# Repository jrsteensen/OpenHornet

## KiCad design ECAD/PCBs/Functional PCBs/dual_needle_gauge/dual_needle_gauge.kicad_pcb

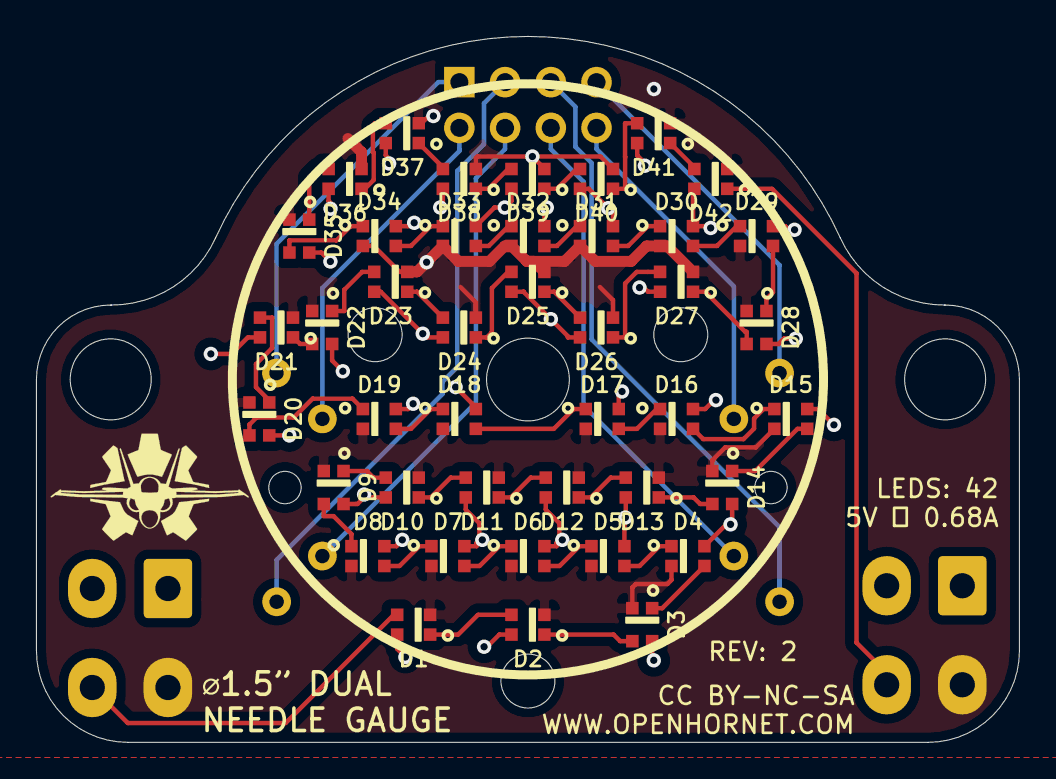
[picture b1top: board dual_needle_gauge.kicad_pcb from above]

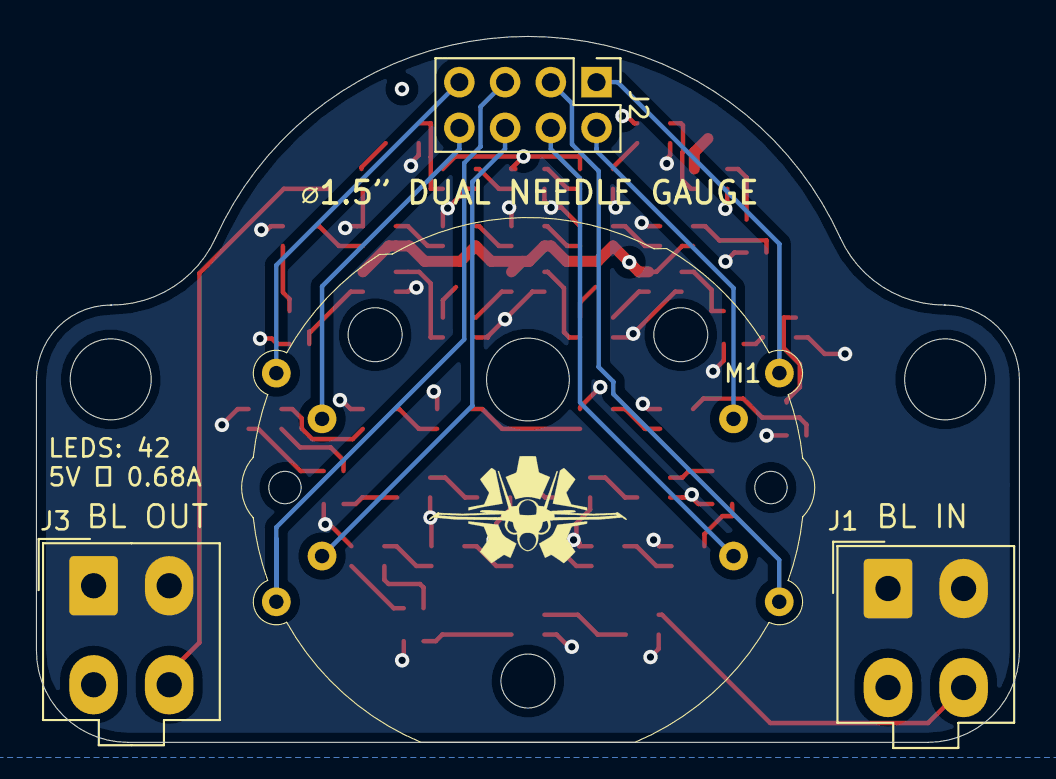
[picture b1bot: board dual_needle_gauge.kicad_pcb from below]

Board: 4 copper layers, 54.6 x 39.2 mm, 48 parts (3 on the bottom side), 53 nets.

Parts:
D1, D2, D3, D4, D5, D6, D7, D8, D9, D10, D11, D12, D13, D14, D15, D16, D17, D18, D19, D20, D21, D22, D23, D24, D25, D26, D27, D28, D29, D30, D31, D32, D33, D34, D35, D36, D37, D38, D39, D40, D41, D42: WS2812B-2020; WS2812-2020
H1, H2: MountingHole; MountingHole_4.5mm
J1: BL IN; Molex_Mini-Fit_Jr_5566-04A_2x02_P4.20mm_Vertical
J2: DATA; PinHeader_2x04_P2.54mm_Vertical
J3: BL OUT; Molex_Mini-Fit_Jr_5566-04A_2x02_P4.20mm_Vertical
M1: X40_8798; x40_8798

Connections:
/COIL1: J2.1, M1.1
/COIL2: J2.3, M1.2
/COIL3: J2.7, M1.3
/COIL4: J2.5, M1.4
/COIL5: J2.2, M1.5
/COIL6: J2.4, M1.6
/COIL7: J2.8, M1.7
/COIL8: J2.6, M1.8
/DIN: D1.3, J1.4
/DOUT: D42.1, J3.4
/DOUT1: D10.1, D11.3
/DOUT2: D20.1, D21.3
/DOUT3: D30.1, D31.3
/DOUT4: D40.1, D41.3
/LED+5V: D1.4, D2.4, D3.4, D4.4, D5.4, D6.4, D7.4, D8.4, D9.4, D10.4, D11.4, D12.4, D13.4, D14.4, D15.4, D16.4, D17.4, D18.4, D19.4, D20.4, D21.4, D22.4, D23.4, D24.4, D25.4, D26.4, D27.4, D28.4, D29.4, D30.4, D31.4, D32.4, D33.4, D34.4, D35.4, D36.4, D37.4, D38.4, D39.4, D40.4, D41.4, D42.4, J1.1, J1.2, J3.1, J3.2
/LEDGND: D1.2, D2.2, D3.2, D4.2, D5.2, D6.2, D7.2, D8.2, D9.2, D10.2, D11.2, D12.2, D13.2, D14.2, D15.2, D16.2, D17.2, D18.2, D19.2, D20.2, D21.2, D22.2, D23.2, D24.2, D25.2, D26.2, D27.2, D28.2, D29.2, D30.2, D31.2, D32.2, D33.2, D34.2, D35.2, D36.2, D37.2, D38.2, D39.2, D40.2, D41.2, D42.2, J1.3, J3.3
unnamed: D1.1, D2.3
unnamed: D2.1, D3.3
unnamed: D3.1, D4.3
unnamed: D4.1, D5.3
unnamed: D5.1, D6.3
unnamed: D6.1, D7.3
unnamed: D7.1, D8.3
unnamed: D8.1, D9.3
unnamed: D9.1, D10.3
unnamed: D11.1, D12.3
unnamed: D12.1, D13.3
unnamed: D13.1, D14.3
unnamed: D14.1, D15.3
unnamed: D15.1, D16.3
unnamed: D16.1, D17.3
unnamed: D17.1, D18.3
unnamed: D18.1, D19.3
unnamed: D19.1, D20.3
unnamed: D21.1, D22.3
unnamed: D22.1, D23.3
unnamed: D23.1, D24.3
unnamed: D24.1, D25.3
unnamed: D25.1, D26.3
unnamed: D26.1, D27.3
unnamed: D27.1, D28.3
unnamed: D28.1, D29.3
unnamed: D29.1, D30.3
unnamed: D31.1, D32.3
unnamed: D32.1, D33.3
unnamed: D33.1, D34.3
unnamed: D34.1, D35.3
unnamed: D35.1, D36.3
unnamed: D36.1, D37.3
unnamed: D37.1, D38.3
unnamed: D38.1, D39.3
unnamed: D39.1, D40.3
unnamed: D41.1, D42.3

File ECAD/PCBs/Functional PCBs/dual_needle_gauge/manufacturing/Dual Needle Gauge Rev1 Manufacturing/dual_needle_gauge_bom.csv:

Comment,Designator,Footprint,LCSC
"WS2812B-2020","D1,D2,D3,D4,D5,D6,D7,D8,D9,D10,D11,D12,D13,D14,D15,D16,D17,D18,D19,D20,D21,D22,D23,D24,D25,D26,D27,D28,D29,D30,D31,D32,D33,D34,D35,D36,D37,D38,D39,D40,D41,D42","KiCAD Libraries:WS2812-2020","C965555"
"MountingHole","H1,H2","MountingHole:MountingHole_4.5mm",""
"BL IN","J1","Connector_Molex:Molex_Mini-Fit_Jr_5566-04A_2x02_P4.20mm_Vertical",""
"DATA","J2","Connector_PinHeader_2.54mm:PinHeader_2x04_P2.54mm_Vertical",""
"BL OUT","J3","Connector_Molex:Molex_Mini-Fit_Jr_5566-04A_2x02_P4.20mm_Vertical",""
"X40_8798","M1","KiCAD Libraries:x40_8798",""

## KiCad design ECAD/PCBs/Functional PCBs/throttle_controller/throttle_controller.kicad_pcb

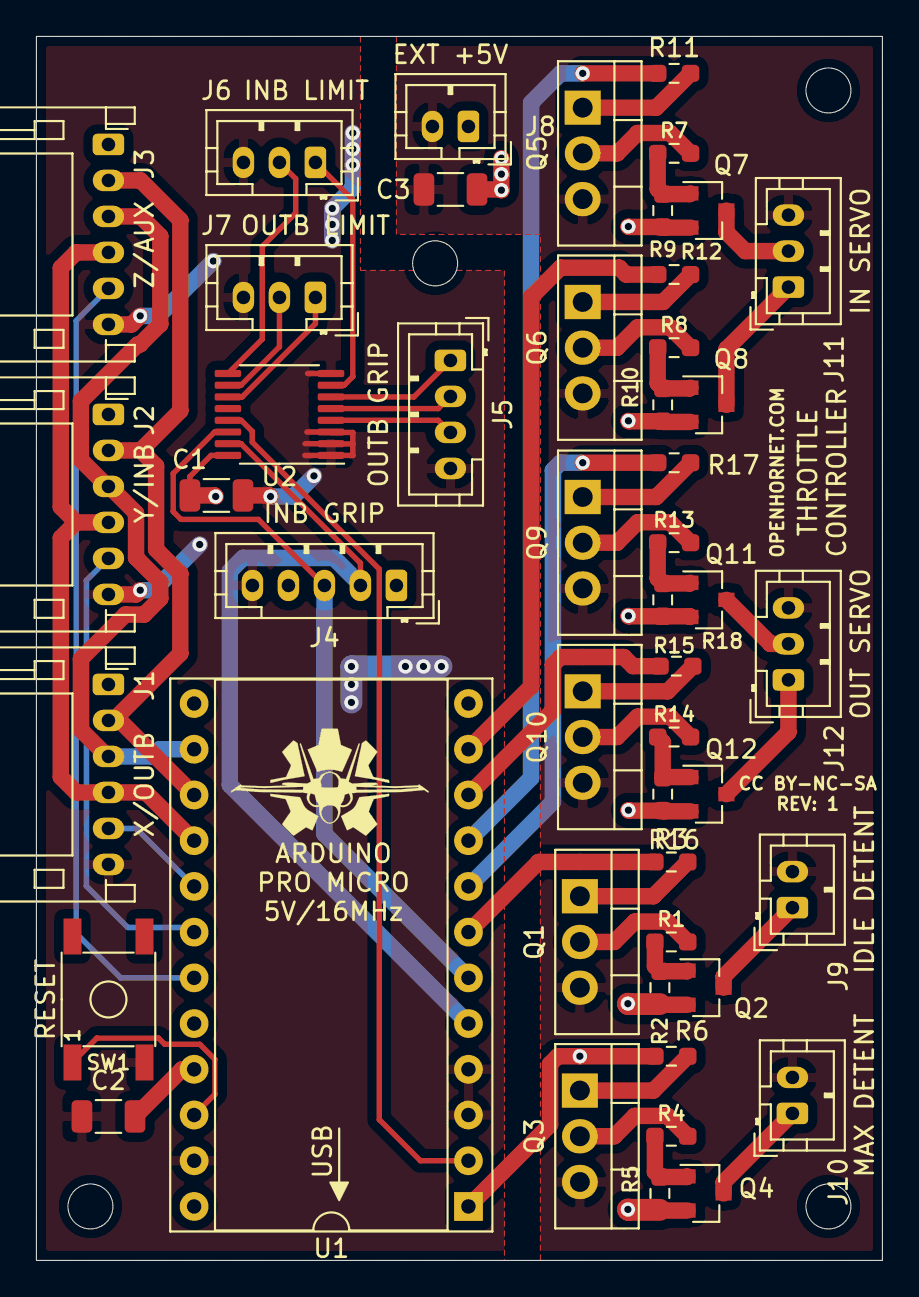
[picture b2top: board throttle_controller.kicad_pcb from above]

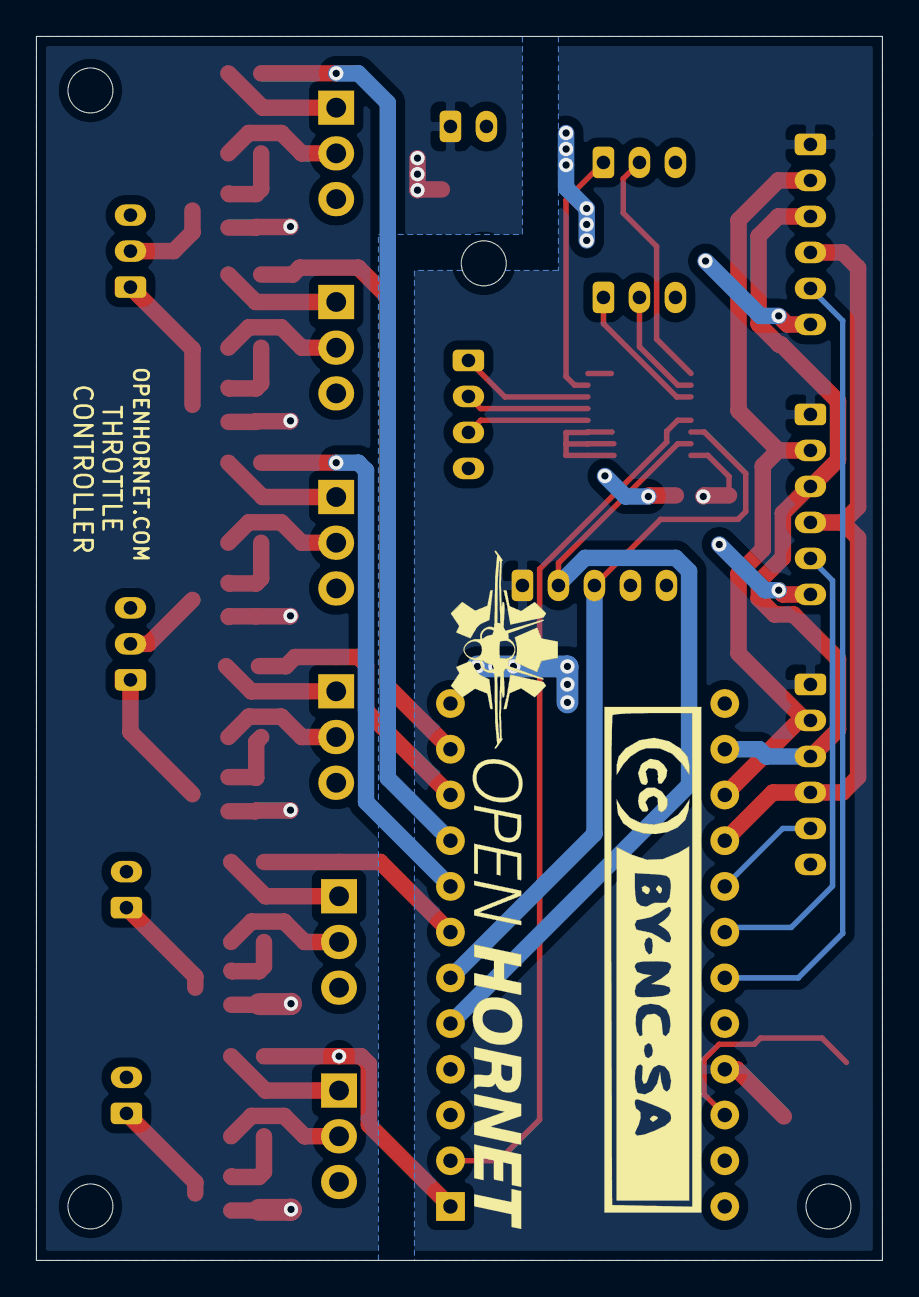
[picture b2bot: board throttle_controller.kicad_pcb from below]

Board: 2 copper layers, 47.0 x 68.0 mm, 55 parts (2 on the bottom side), 51 nets.

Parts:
C1: 47uF; C_1206_3216Metric
C2, C3: 10uF; C_1206_3216Metric
H1, H2, H3, H4: MH; MountingHole_2.5mm
J1: X/OUTB; JST_PH_S6B-PH-K_1x06_P2.00mm_Horizontal
J2: Y/INB; JST_PH_S6B-PH-K_1x06_P2.00mm_Horizontal
J3: Z/AUX; JST_PH_S6B-PH-K_1x06_P2.00mm_Horizontal
J4: INB GRIP; JST_PH_B5B-PH-K_1x05_P2.00mm_Vertical
J5: OUTB GRIP; JST_PH_B4B-PH-K_1x04_P2.00mm_Vertical
J6: INB LIMIT; JST_PH_B3B-PH-K_1x03_P2.00mm_Vertical
J7: OUTB LIMIT; JST_PH_B3B-PH-K_1x03_P2.00mm_Vertical
J8: EXT +5V; JST_PH_B2B-PH-K_1x02_P2.00mm_Vertical
J9: IDLE DETENT; JST_PH_B2B-PH-K_1x02_P2.00mm_Vertical
J10: MAX DETENT; JST_PH_B2B-PH-K_1x02_P2.00mm_Vertical
J11: IN SERVO; JST_PH_B3B-PH-K_1x03_P2.00mm_Vertical
J12: OUT SERVO; JST_PH_B3B-PH-K_1x03_P2.00mm_Vertical
LOGO1: OpenHornetLogoSmall; OH_LOGO_37.7mm_5.9mm
LOGO2: OpenHornetLogoSmall; CC-BY-NC-SA-Small
LOGO3: OpenHornetLogoSmall; OH_LOGO_ONLY_11x6mm
Q1, Q3, Q5, Q6, Q9, Q10: IRFB3206PBF; TO-220-3_Vertical
Q2, Q4, Q7, Q8, Q11, Q12: IRLML6402TRPBF; SOT-23
R1, R2, R3, R4, R5, R6, R7, R8, R9, R10, R11, R12, R13, R14, R15, R16, R17, R18: 10K; R_0603_1608Metric_Pad0.98x0.95mm_HandSolder
SW1: RESET; SMD-SW-4_5.1x5.1
U1: ProMicro; DIP-24_W15.24mm_Socket
U2: TCA9554PWR; TSSOP-16_4.4x5mm_P0.65mm

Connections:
+5V: C1.1, C2.1, J1.1, J2.1, J3.1, J4.1, U1.21, U2.16
+5VA: C3.1, J8.1, Q2.2, Q4.2, Q7.2, Q8.2, Q11.2, Q12.2, R2.2, R5.2, R9.2, R10.2, R15.2, R16.2
/CSx: J1.5, U1.17
/CSy: J2.5, U1.18
/CSz: J3.5, U1.19
/IDLE_SOL_CTRL: R3.1, U1.7
/IDLE_SOL_OUT: J9.1, Q2.3
/INB_SERVO_+5VA: J11.1, Q8.3
/INB_SERVO_PWR_CTRL: R12.1, U1.11
/IRQ: U1.2, U2.13
/MAX_SOL_CTRL: R6.1, U1.1
/MAX_SOL_OUT: J10.1, Q4.3
/MISO: J1.2, J2.2, J3.2, U1.15
/MOSI: J1.3, J2.3, J3.3, U1.14
/OUTB_SERVO_+5VA: J12.1, Q12.3
/OUTB_SERVO_PWR_CTRL: R18.1, U1.10
/RST: SW1.1, U1.22
/SCK: J1.4, J2.4, J3.4, U1.16
/SDA: J4.2, U1.5, U2.15
/U1P0: J5.1, U2.6
/U1P1: J5.2, U2.5
/U1P2: J5.3, U2.4
/U1P3: J6.1, U2.7
/U1P4: J6.2, U2.9
/U1P5: J7.2, U2.10
/U1P6: J7.1, U2.11
/~INB_SERVO_CTRL: R11.1, U1.9
/~INB_SERVO_OUT: J11.2, Q7.3
/~OUTB_SERVO_CTRL: R17.1, U1.8
/~OUTB_SERVO_OUT: J12.2, Q11.3
/~SCL: J4.3, U1.6, U2.14
GND: C1.2, C2.2, J1.6, J2.6, J3.6, J4.5, J5.4, J6.3, J7.3, SW1.3, U1.3, U1.4, U1.23, U2.1, U2.2, U2.3, U2.8
GNDA: C3.2, J8.2, J9.2, J10.2, J11.3, J12.3, Q1.3, Q3.3, Q5.3, Q6.3, Q9.3, Q10.3
unnamed: Q1.1, R3.2
unnamed: Q1.2, R1.2
unnamed: Q2.1, R1.1, R2.1
unnamed: Q3.1, R6.2
unnamed: Q3.2, R4.2
unnamed: Q4.1, R4.1, R5.1
unnamed: Q5.1, R11.2
unnamed: Q5.2, R7.2
unnamed: Q6.1, R12.2
unnamed: Q6.2, R8.2
unnamed: Q7.1, R7.1, R9.1
unnamed: Q8.1, R8.1, R10.1
unnamed: Q9.1, R17.2
unnamed: Q9.2, R13.2
unnamed: Q10.1, R18.2
unnamed: Q10.2, R14.2
unnamed: Q11.1, R13.1, R15.1
unnamed: Q12.1, R14.1, R16.1

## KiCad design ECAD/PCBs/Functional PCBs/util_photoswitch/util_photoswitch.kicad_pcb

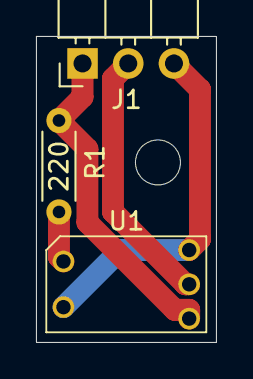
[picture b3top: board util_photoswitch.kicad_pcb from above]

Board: 2 copper layers, 10.0 x 17.0 mm, 4 parts (0 on the bottom side), 4 nets.

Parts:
H1: MountingHole; MountingHole_2.5mm
J1: Conn_01x03_Male; PinHeader_1x03_P2.54mm_Horizontal
R1: 220; R_Axial_DIN0204_L3.6mm_D1.6mm_P5.08mm_Horizontal
U1: OPB615; OPB61x

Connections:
+5V: J1.1, R1.2, U1.3
GND: J1.3, U1.2, U1.5
unnamed: J1.2, U1.4
unnamed: R1.1, U1.1

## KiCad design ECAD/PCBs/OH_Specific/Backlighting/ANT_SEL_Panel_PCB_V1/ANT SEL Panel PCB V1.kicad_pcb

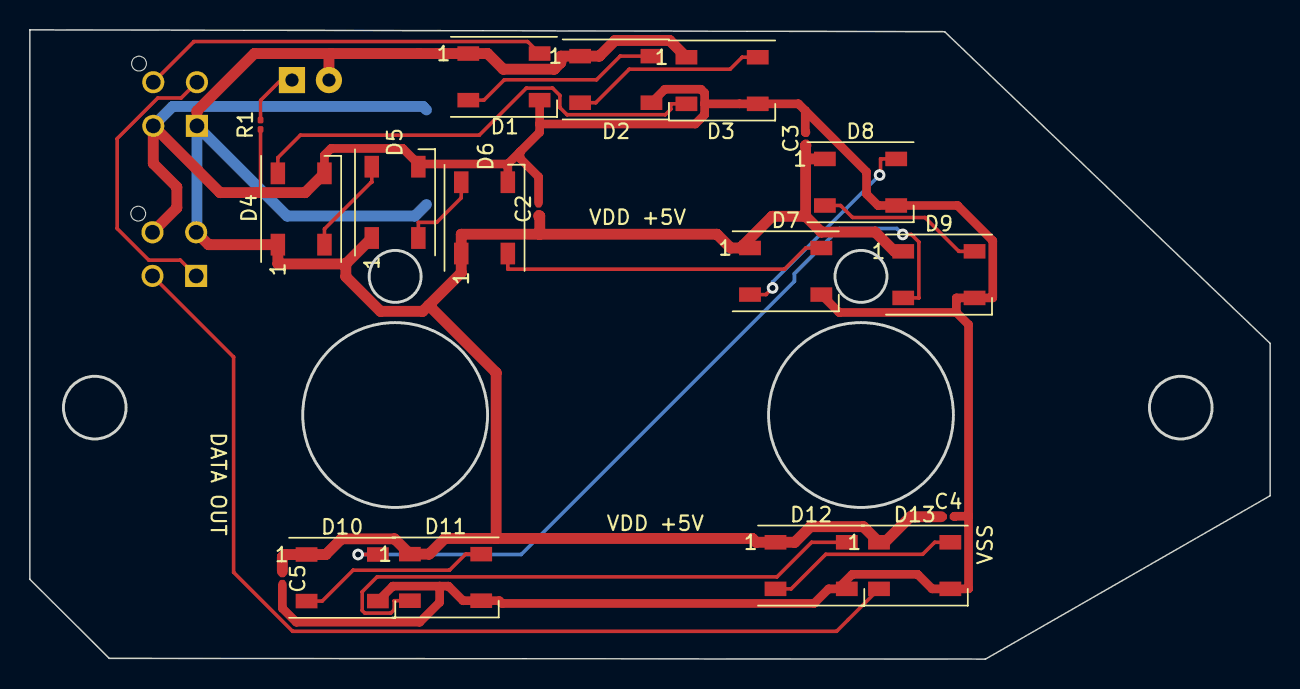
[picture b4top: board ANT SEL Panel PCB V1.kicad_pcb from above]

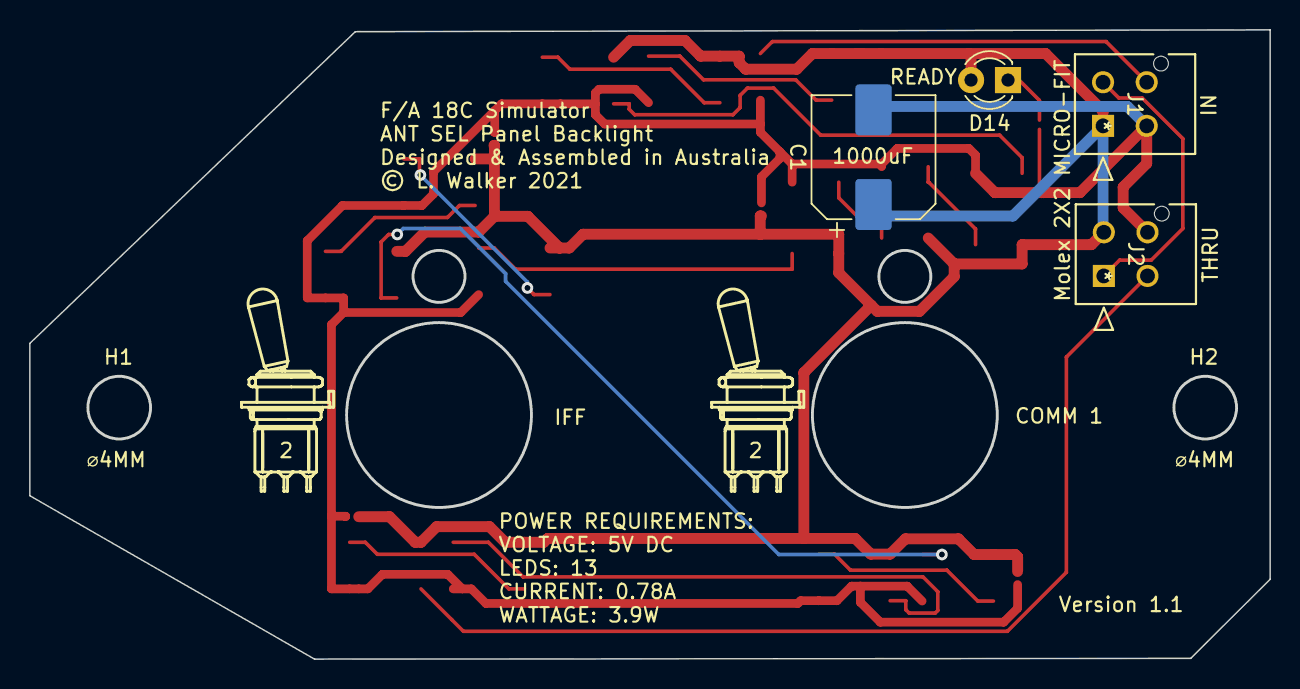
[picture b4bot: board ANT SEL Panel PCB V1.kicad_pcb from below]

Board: 2 copper layers, 85.2 x 43.2 mm, 22 parts (4 on the bottom side), 18 nets.

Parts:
C1: C_Polarized; CP_Elec_8x10
C2, C3, C4, C5: C; C_0201_0603Metric
D1, D2, D3, D4, D5, D6, D7, D8, D9, D10, D11, D12, D13: WS2812B; LED_WS2812B_PLCC4_5.0x5.0mm_P3.2mm
D14: LED; LED_D3.0mm
J1, J2: Conn_01x04_Female; Molex_MicroFit_2X2
R1: R; R_0201_0603Metric

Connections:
/LED+5V: C1.1, C2.1, C3.1, C4.1, C5.1, D1.1, D2.1, D3.1, D4.1, D5.1, D6.1, D7.1, D8.1, D9.1, D10.1, D11.1, D12.1, D13.1, D14.2, J1.1, J2.2
/LEDGND: C1.2, C2.2, C3.2, C4.2, C5.2, D1.3, D2.3, D3.3, D4.3, D5.3, D6.3, D7.3, D8.3, D9.3, D10.3, D11.3, D12.3, D13.3, J1.3, J2.4, R1.1
unnamed: D1.2, D2.4
unnamed: D1.4, J1.4
unnamed: D2.2, D3.4
unnamed: D3.2, D4.4
unnamed: D4.2, D5.4
unnamed: D5.2, D6.4
unnamed: D6.2, D7.4
unnamed: D7.2, D8.4
unnamed: D8.2, D9.4
unnamed: D10.2, D11.4
unnamed: D9.2, D10.4
unnamed: D11.2, D12.4
unnamed: D12.2, D13.4
unnamed: D13.2, J2.3
unnamed: D14.1, R1.2
unnamed: J1.2, J2.1

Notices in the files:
ECAD/PCBs/OH_Specific/Backlighting/ANT_SEL_Panel_PCB_V1/ANT SEL Panel PCB V1.kicad_pcb:
© L. Walker 2021
parts and their libraries:
Copyright 2016 Accelerated Designs. All rights reserved.
